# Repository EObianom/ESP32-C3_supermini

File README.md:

# ESP32-C3_supermini

Ultra-Compact ESP32-C3 Development Board

A minimal, production-ready ESP32-C3 hardware design built from the bare chip, not a prepackaged module. Designed for engineers who prefer precision over excess.

Small footprint. Full capability. No shortcuts.

## Overview:

This project implements a highly compact ESP32-C3-based development board, designed from the ground up using the ESP32-C3 chip rather than a ready-made module. By eliminating unnecessary overhead and integrating a compact antenna based on manufacturer specifications, the design significantly reduces board size while maintaining reliable wireless performance.

The result is a lean, flexible, and fully manufacturable platform for embedded and IoT applications where space, control, and efficiency matter.

## Features:
- Ultra-compact PCB design (25mm × 27.8mm) optimised for space-constrained applications
- Built around the ESP32-C3 SoC (RISC-V architecture, Wi-Fi + Bluetooth LE)
- Uses a compact CA-C03 antenna based on manufacturer reference design
- No prebuilt module, full control over hardware design and layout
- Carefully designed RF layout for stable wireless performance
- USB interface for programming and power
- Low component count for cost-effective manufacturing
- Fully production-ready design files included

## Repository Contents
This repository provides a complete hardware package ready for fabrication and assembly:

1. Schematic
2. PCB Layout: Compact and optimised routing, including RF considerations
3. Footprints
4. Gerber Files: Ready-to-manufacture PCB fabrication files
5. BOM (JLC Format): Bill of Materials.
6. CPL File: Pick-and-place file for automated component assembly.

## Getting Started:
1. Review the schematic to understand system design and component choices
2. Open the PCB layout in KiCad to inspect placement and routing
3. Generate or use provided Gerber files to order your PCB
4. Upload the BOM and CPL files to JLCPCB (or similar) for assembly
5. Flash firmware via USB and begin development

Once assembled, the board can be programmed using standard ESP32-C3 toolchains such as ESP-IDF or Arduino.

## Applications:
- IoT devices
- Wearable electronics
- Embedded wireless systems
- Smart sensors and edge devices
- Custom ESP32-based product development

---
Disclaimer: This design is intended for research, development, and prototyping purposes only. Ensure proper RF compliance and certification before using in commercial products. This work is licensed under a Creative Commons Attribution-NonCommercial 4.0 International License.

Contributions and improvements are welcome. Feel free to open an issue or submit a pull request.

Designed and developed by Ekenedirichukwu Obianom

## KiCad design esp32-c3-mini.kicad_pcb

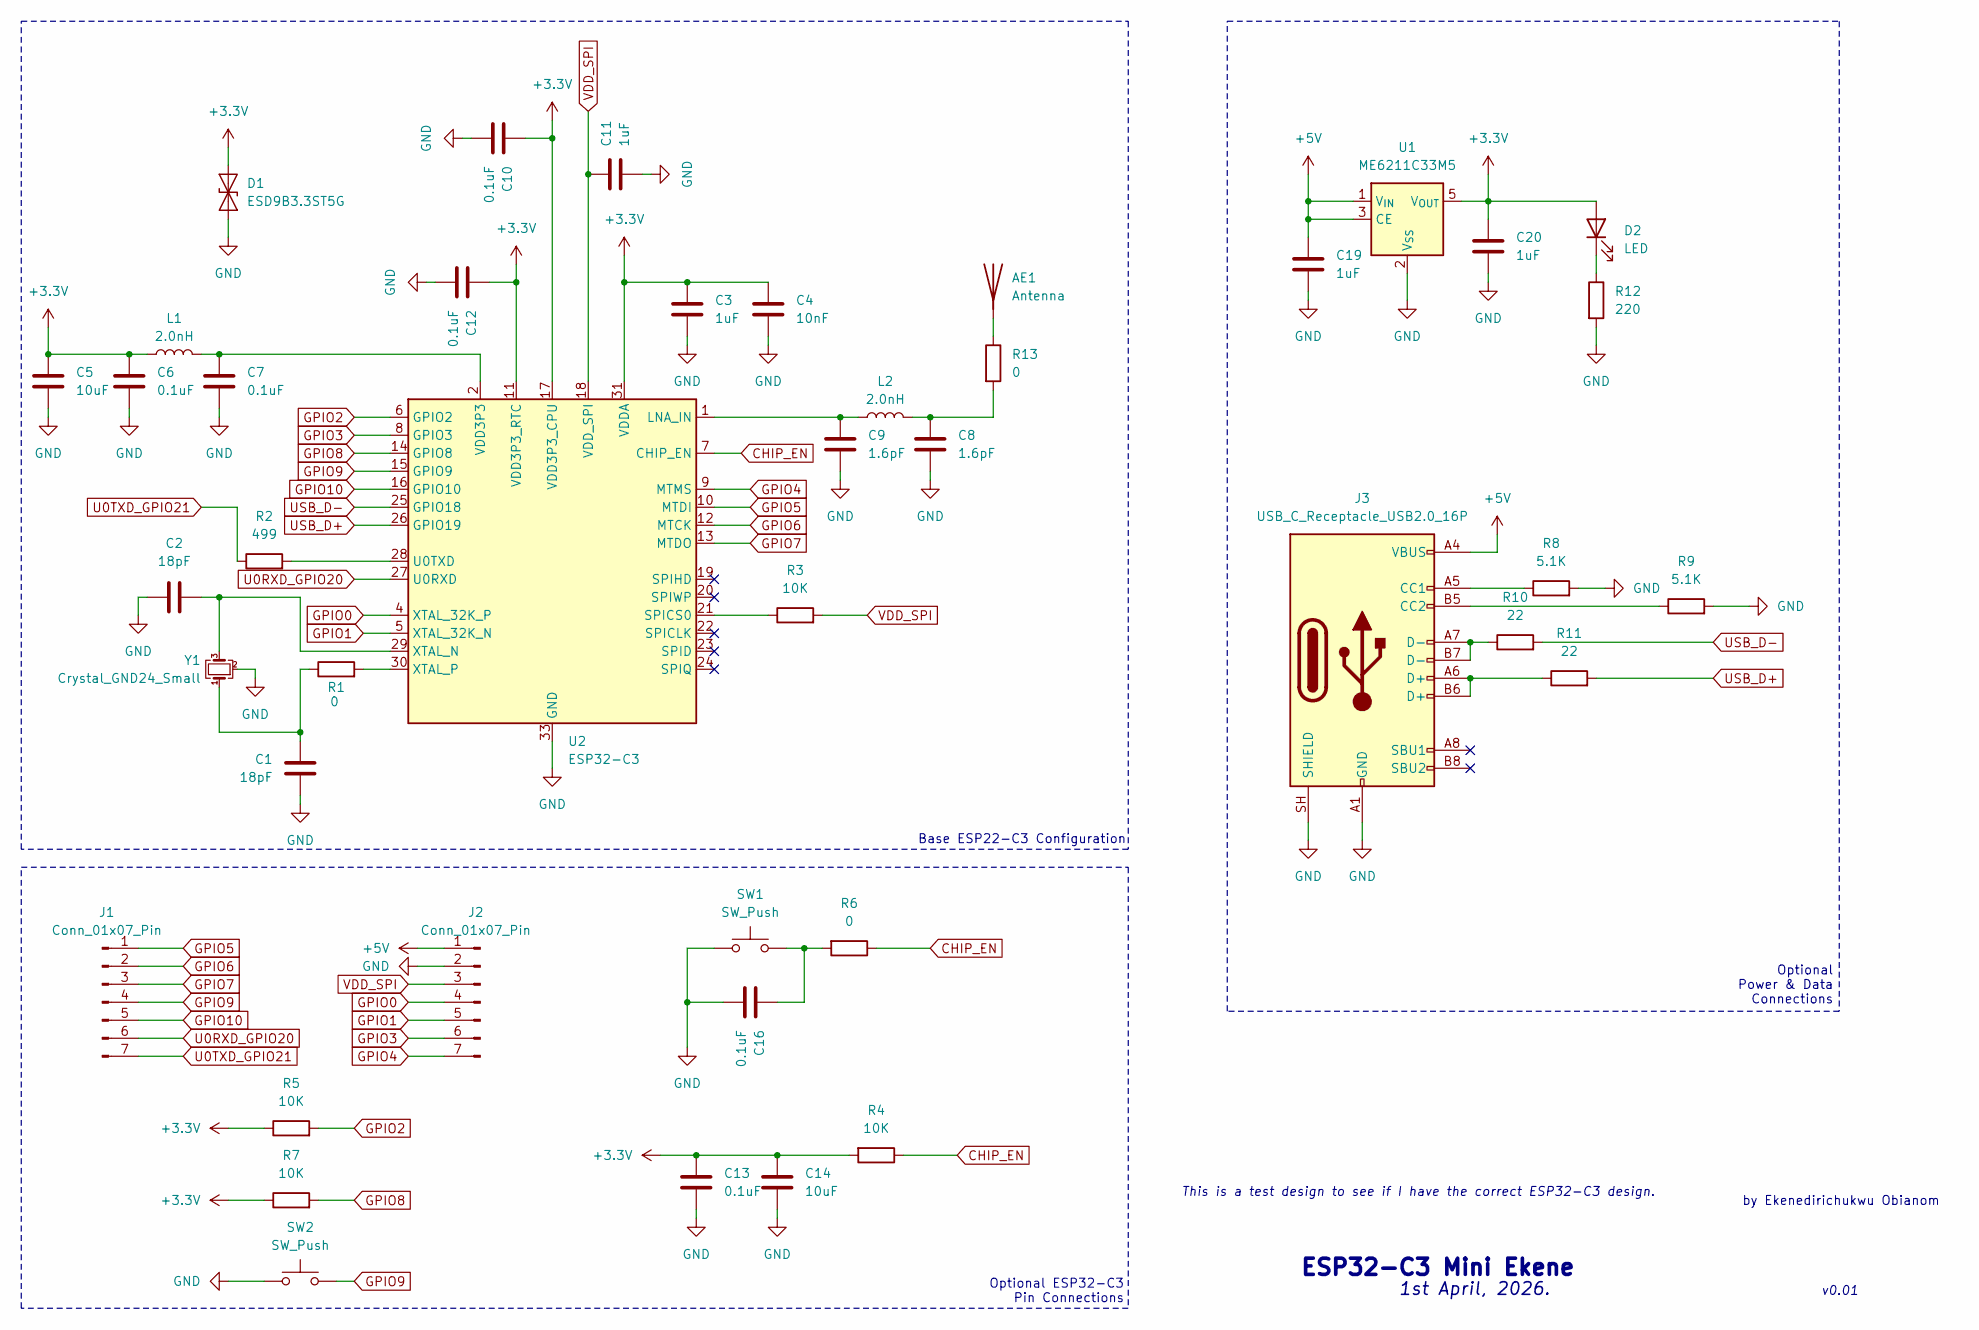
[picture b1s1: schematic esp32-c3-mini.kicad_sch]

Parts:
AE1: Antenna; CA-C03_SMD_Antenna
C1, C2: 18pF; C_0402_1005Metric
C3, C11, C19, C20: 1uF; C_0603_1608Metric
C4: 10nF; C_0603_1608Metric
C5, C14: 10uF; C_0603_1608Metric
C6, C7, C10, C12, C13, C16: 0.1uF; C_0402_1005Metric
C8, C9: 1.6pF; C_0603_1608Metric
D1: ESD9B3.3ST5G; D_SOD-923
D2: LED; LED_0603_1608Metric
J1, J2: Conn_01x07_Pin; PinHeader_1x07_P2.54mm_Vertical
J3: USB_C_Receptacle_USB2.0_16P; USB_C_Receptacle_HRO_TYPE-C-31-M-12
L1, L2: 2.0nH; L_0402_1005Metric
R1, R6, R13: 0; R_0603_1608Metric
R2: 499; R_0402_1005Metric
R3, R4, R5, R7: 10K; R_0603_1608Metric
R8, R9: 5.1K; R_0402_1005Metric
R10, R11: 22; R_0402_1005Metric
R12: 220; R_0402_1005Metric
SW1, SW2: SW_Push; SW_Push_SPST_NO_Alps_SKRK
U1: ME6211C33M5; SOT-23-5
U2: ESP32-C3; QFN-32-1EP_5x5mm_P0.5mm_EP3.7x3.7mm
Y1: Crystal_GND24_Small; Crystal_SMD_3225-4Pin_3.2x2.5mm

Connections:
+3.3V: C3.1, C4.1, C5.1, C6.1, C10.1, C12.1, C13.1, C14.1, C20.1, D1.2 (A2), D2.2 (A), L1.1, R4.2, R5.1, R7.1, U1.5 (V_{OUT}), U2.11 (VDD3P3_RTC), U2.17 (VDD3P3_CPU), U2.31 (VDDA), U2.32 (VDDA)
+5V: C19.1, J2.1, J3.A4 (VBUS), J3.A9 (VBUS), J3.B4 (VBUS), J3.B9 (VBUS), U1.1 (V_{IN}), U1.3 (CE)
CHIP_EN: R4.1, R6.1, U2.7 (CHIP_EN)
GND: C1.1, C2.2, C3.2, C4.2, C5.2, C6.2, C7.2, C8.2, C9.2, C10.2, C11.2, C12.2, C13.2, C14.2, C16.2, C19.2, C20.2, D1.1 (A1), J2.2, J3.A1 (GND), J3.A12 (GND), J3.B1 (GND), J3.B12 (GND), J3.SH (SHIELD), R8.2, R9.2, R12.2, SW1.1, SW2.1, U1.2 (V_{SS}), U2.33 (GND), Y1.2 (G), Y1.4 (G)
GPIO0: J2.4, U2.4 (XTAL_32K_P)
GPIO1: J2.5, U2.5 (XTAL_32K_N)
GPIO2: R5.2, U2.6 (GPIO2)
GPIO3: J2.6, U2.8 (GPIO3)
GPIO4: J2.7, U2.9 (MTMS)
GPIO5: J1.1, U2.10 (MTDI)
GPIO6: J1.2, U2.12 (MTCK)
GPIO7: J1.3, U2.13 (MTDO)
GPIO8: R7.2, U2.14 (GPIO8)
GPIO9: J1.4, SW2.2, U2.15 (GPIO9)
GPIO10: J1.5, U2.16 (GPIO10)
unnamed: AE1.1 (A_1), R13.1
unnamed: C1.2, R1.1, Y1.1
unnamed: C7.1, L1.2, U2.2 (VDD3P3), U2.3 (VDD3P3)
unnamed: C8.1, L2.1, R13.2
unnamed: C16.1, R6.2, SW1.2
unnamed: D2.1 (K), R12.1
unnamed: J3.A5 (CC1), R8.1
unnamed: J3.B5 (CC2), R9.1
unnamed: J3.A6 (D+), J3.B6 (D+), R11.1
unnamed: J3.A7 (D-), J3.B7 (D-), R10.1
unnamed: C9.1, L2.2, U2.1 (LNA_IN)
unnamed: R3.1, U2.21 (SPICS0)
unnamed: R2.2, U2.28 (U0TXD)
unnamed: C2.1, U2.29 (XTAL_N), Y1.3
unnamed: R1.2, U2.30 (XTAL_P)
U0RXD_GPIO20: J1.6, U2.27 (U0RXD)
U0TXD_GPIO21: J1.7, R2.1
USB_D+: R11.2, U2.26 (GPIO19)
USB_D-: R10.2, U2.25 (GPIO18)
VDD_SPI: C11.1, J2.3, R3.2, U2.18 (VDD_SPI)

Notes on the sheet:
Base ESP22-C3 Configuration
1st April, 2026.
This is a test design to see if I have the correct ESP32-C3 design.
Optional ESP32-C3 Pin Connections
v0.01
ESP32-C3 Mini Ekene
by Ekenedirichukwu Obianom
Optional Power & Data Connections

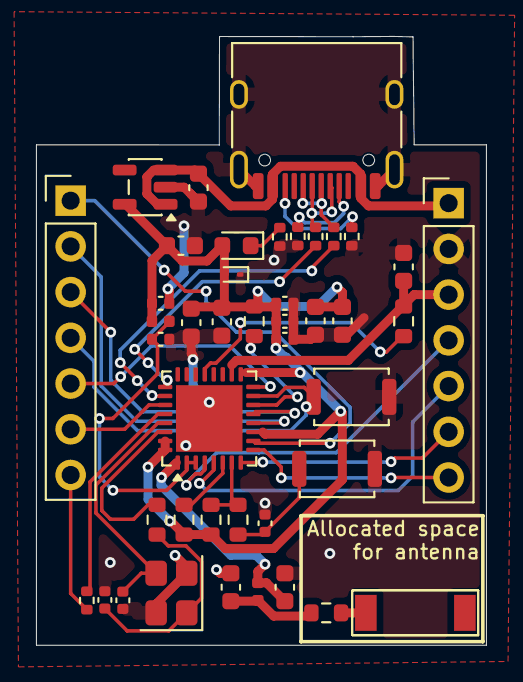
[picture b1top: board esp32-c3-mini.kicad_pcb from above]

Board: 4 copper layers, 25.0 x 33.8 mm, 43 parts (0 on the bottom side), 35 nets.

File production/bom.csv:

Designator,Footprint,Quantity,Value,LCSC Part #
AE1,CA-C03_SMD_Antenna,1,Antenna,
"C1, C2",0402,2,18pF,
"C10, C12, C13, C16, C6, C7",0402,6,0.1uF,
"C11, C19, C20, C3",0603,4,1uF,
"C14, C5",0603,2,10uF,
C4,0603,1,10nF,
"C8, C9",0603,2,1.6pF,
D1,D_SOD-923,1,ESD9B3.3ST5G,
D2,0603,1,LED,
"J1, J2",PinHeader_1x07_P2.54mm_Vertical,2,Conn_01x07_Pin,
J3,USB_C_Receptacle_HRO_TYPE-C-31-M-12,1,USB_C_Receptacle_USB2.0_16P,
"L1, L2",0402,2,2.0nH,
"R1, R13, R6",0603,3,0,
"R10, R11",0402,2,22,
R12,0402,1,220,
R2,0402,1,499,
"R3, R4, R5, R7",0603,4,10K,
"R8, R9",0402,2,5.1K,
"SW1, SW2",SW_Push_SPST_NO_Alps_SKRK,2,SW_Push,
U1,SOT-23-5,1,ME6211C33M5,
U2,QFN-32-1EP_5x5mm_P0.5mm_EP3.7x3.7mm,1,ESP32-C3,
Y1,Crystal_SMD_3225-4Pin_3.2x2.5mm,1,Crystal_GND24_Small,

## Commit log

2026-04-08 Add ESP32-C3 mini KiCad project and gerbers
    Add a new KiCad project for the ESP32-C3 Mini including project file (.kicad_pro), schematic (.kicad_sch), PCB (.kicad_pcb), and library entries (fp-lib-table and CA-C03_SMD_Antenna footprint). Also 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
2026-04-08 Add image to README for ESP32-C3 supermini
2026-04-08 Enhance README with detailed project information
    Expanded the README to include an overview, features, repository contents, getting started guide, applications, and a disclaimer, enhancing clarity and usability.
2026-04-08 Enhance README with BOM and CPL file information
    Added BOM and CPL file details to the README and updated assembly instructions.
2026-04-08 Adjust solder mask and add production files
    Remove explicit solder_mask_min_width from PCB file and update project settings to set solder_mask_to_copper_clearance to 0.005. Add fabrication-toolkit-options.json and generated production artifact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
2026-04-08 Add Creative Commons license
    Added the Creative Commons Attribution-NonCommercial-NoDerivatives 4.0 International Public License to the project.
2026-04-08 Add licensing details to README
    Added licensing information to the README.
2026-04-08 Revise disclaimer and licensing information in README
    Updated the disclaimer to include licensing information and removed redundant license statement.
2026-04-09 Add production BOM/designators/positions CSVs
    Add production artifacts for PCB assembly: production/bom.csv (bill of materials), production/designators.csv (component counts), and production/positions.csv (pick-and-place coordinates).
    Also update .gitignore to stop excluding exported BOM files (*.xml, *.csv) so these production CSVs can be committed. These files provide necessary data for procurement and assembly.
2026-04-13 Replace USB plug with USB-C receptacle
    Replace the previous USB plug footprint with a USB_C_Receptacle_HRO_TYPE-C-31-M-12 footprint (USB2.0/PD). Update pad geometry, positions, orientations, silkscreen and UUIDs; remap nets/pin names from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
2026-04-14 Replace image in README with updated version
    Updated image in README.md to a new source.
2026-05-11 Rotate USB-C footprint and update routing
    Rotate the USB-C receptacle footprint 180° (update (at) coordinates and properties), mirror/update silkscreen/courtyard/fab lines and refresh fp UUIDs. Add/adjust board routing: new traces, vias and 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
2026-05-13 Add ImageCopy.png and PrintCopy.pdf
    Add two binary assets: ImageCopy.png and PrintCopy.pdf. These files provide image and printable PDF copies used by the project (added as new assets).
